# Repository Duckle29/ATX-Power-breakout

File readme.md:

# Pi ATX power breakout

This is just a simple board that breaks out the different rails of an ATX 24pin connector. It's mainly intented to be used for powering a Raspberry Pi and a 3D printer.

The board includes an EPS 4pin connector as well, allowing for up to 32A on the 12v rail. If you slightly overrun the rated 8A per cable, the 3 12v connectors will handle up to 36A (12A each). This is a 12.5% overload at 9A per cable. Most good cables/connectors should handle that.

The other rails can output 12A max, if the PSU can supply that on that rail.

The board also has a header for selecting how to control the PS_ON signal. It can either be controlled via a transistor controled by the RPi. Aditionally, the "Power Good" signal is also connected to the pi (through a voltage dividier).
Lastly, the I2C interface of the Pi is exposed on a 5 pin header, along with 5V 3V3 and Ground.

The 5V supply for the I2C connector and the Pi is selected through the the jumper JP1, while the 5V supply for the USB connector is selected via JP2. You can select between the 5V rail, or the 5V standby rail.

| Pin   | Function   |
|-------|------------|
| BCM17 | Power Good |
| BCM9  | Power On   |
| BCM26 | BTN to GND |

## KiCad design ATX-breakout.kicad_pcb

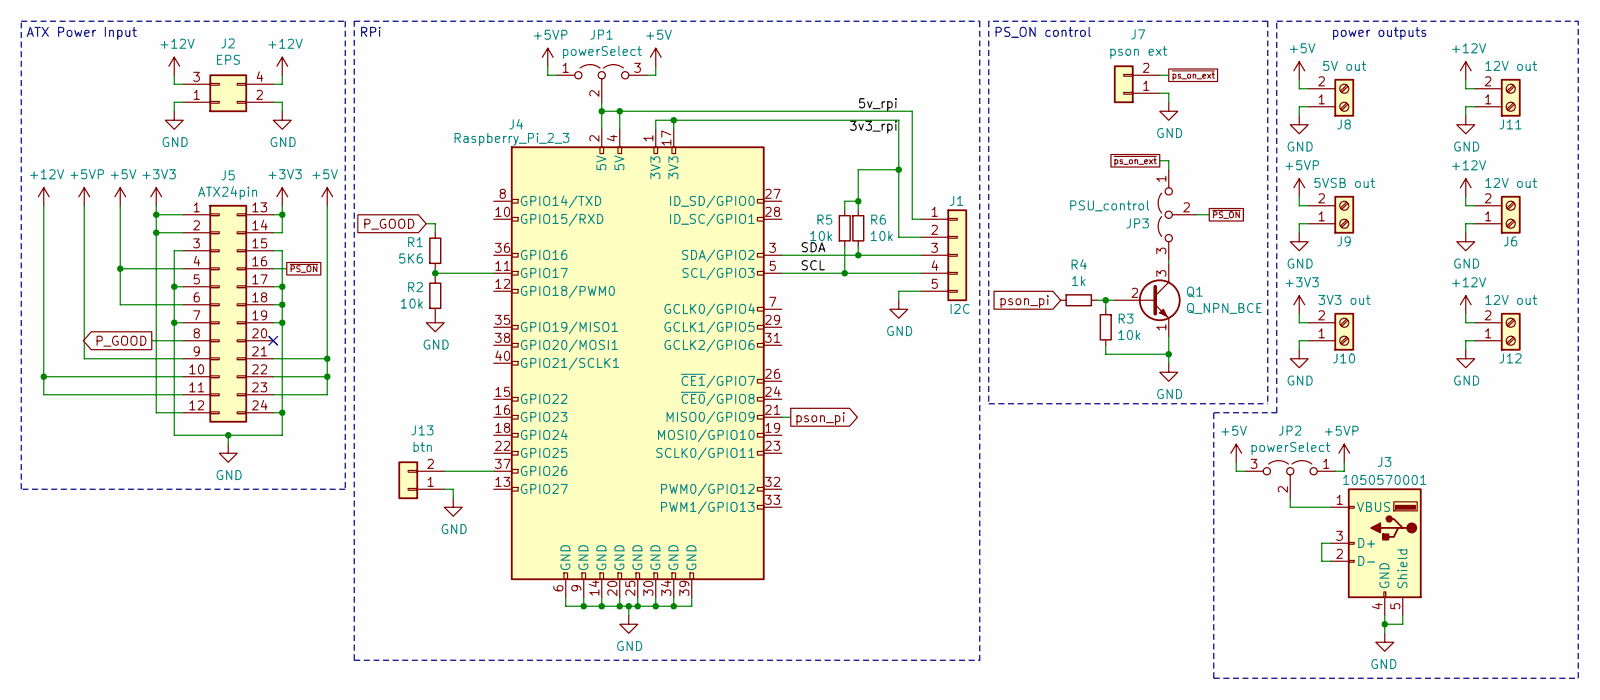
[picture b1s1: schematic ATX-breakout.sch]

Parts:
J1: I2C; PinHeader_1x05_P2.54mm_Vertical
J2: EPS; Molex_Mini-Fit_Jr_5566-04A_2x02_P4.20mm_Vertical
J3: 1050570001; USB_A_Molex_105057_Vertical
J4: Raspberry_Pi_2_3; PinSocket_2x20_P2.54mm_Vertical
J5: ATX24pin; Molex_Mini-Fit_Jr_5566-24A_2x12_P4.20mm_Vertical
J6, J11, J12: 12V out; PhoenixContact_MSTBA_2,5_2-G_1x02_P5.00mm_Horizontal
J7: pson ext; PinHeader_1x02_P2.54mm_Vertical
J8: 5V out; PhoenixContact_MSTBA_2,5_2-G_1x02_P5.00mm_Horizontal
J9: 5VSB out; PhoenixContact_MSTBA_2,5_2-G_1x02_P5.00mm_Horizontal
J10: 3V3 out; PhoenixContact_MSTBA_2,5_2-G_1x02_P5.00mm_Horizontal
J13: btn; PinHeader_1x02_P2.54mm_Vertical
JP1, JP2: powerSelect; PinHeader_1x03_P2.54mm_Vertical
JP3: PSU_control; PinHeader_1x03_P2.54mm_Vertical
Q1: Q_NPN_BCE; TO-92
R1: 5K6; R_Axial_DIN0207_L6.3mm_D2.5mm_P7.62mm_Horizontal
R2, R3, R5, R6: 10k; R_Axial_DIN0207_L6.3mm_D2.5mm_P7.62mm_Horizontal
R4: 1k; R_Axial_DIN0207_L6.3mm_D2.5mm_P7.62mm_Horizontal

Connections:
+3V3: J5.1, J5.2, J5.12, J5.13, J5.14, J10.2
+5V: J5.4, J5.6, J5.21, J5.22, J5.23, J8.2, JP1.3 (B), JP2.3 (B)
+5VP: J5.9, J9.2, JP1.1 (A), JP2.1 (A)
+12V: J2.3, J2.4, J5.10, J5.11, J6.2, J11.2, J12.2
/3v3_rpi: J1.2, J4.1 (3V3), J4.17 (3V3), R5.2, R6.1
/5v_rpi: J1.1, J4.2 (5V), J4.4 (5V), JP1.2 (C)
/SCL: J1.4, J4.5 (SCL/GPIO3), R5.1
/SDA: J1.3, J4.3 (SDA/GPIO2), R6.2
GND: J1.5, J2.1, J2.2, J3.4 (GND), J3.5 (Shield), J4.6 (GND), J4.9 (GND), J4.14 (GND), J4.20 (GND), J4.25 (GND), J4.30 (GND), J4.34 (GND), J4.39 (GND), J5.3, J5.5, J5.7, J5.15, J5.17, J5.18, J5.19, J5.24, J6.1, J7.1, J8.1, J9.1, J10.1, J11.1, J12.1, J13.1, Q1.1 (E), R2.1, R3.2
unnamed: J3.1 (VBUS), JP2.2 (C)
unnamed: J3.2 (D-), J3.3 (D+)
unnamed: J4.11 (GPIO17), R1.1, R2.2
unnamed: J4.37 (GPIO26), J13.2
unnamed: JP3.3 (B), Q1.3 (C)
unnamed: Q1.2 (B), R3.1, R4.2
P_GOOD: J5.8, R1.2
pson_pi: J4.21 (MISO0/GPIO9), R4.1
~PS_ON: J5.16, JP3.2 (C)
~ps_on_ext: J7.2, JP3.1 (A)

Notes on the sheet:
power outputs
PS_ON control
ATX Power Input
RPi

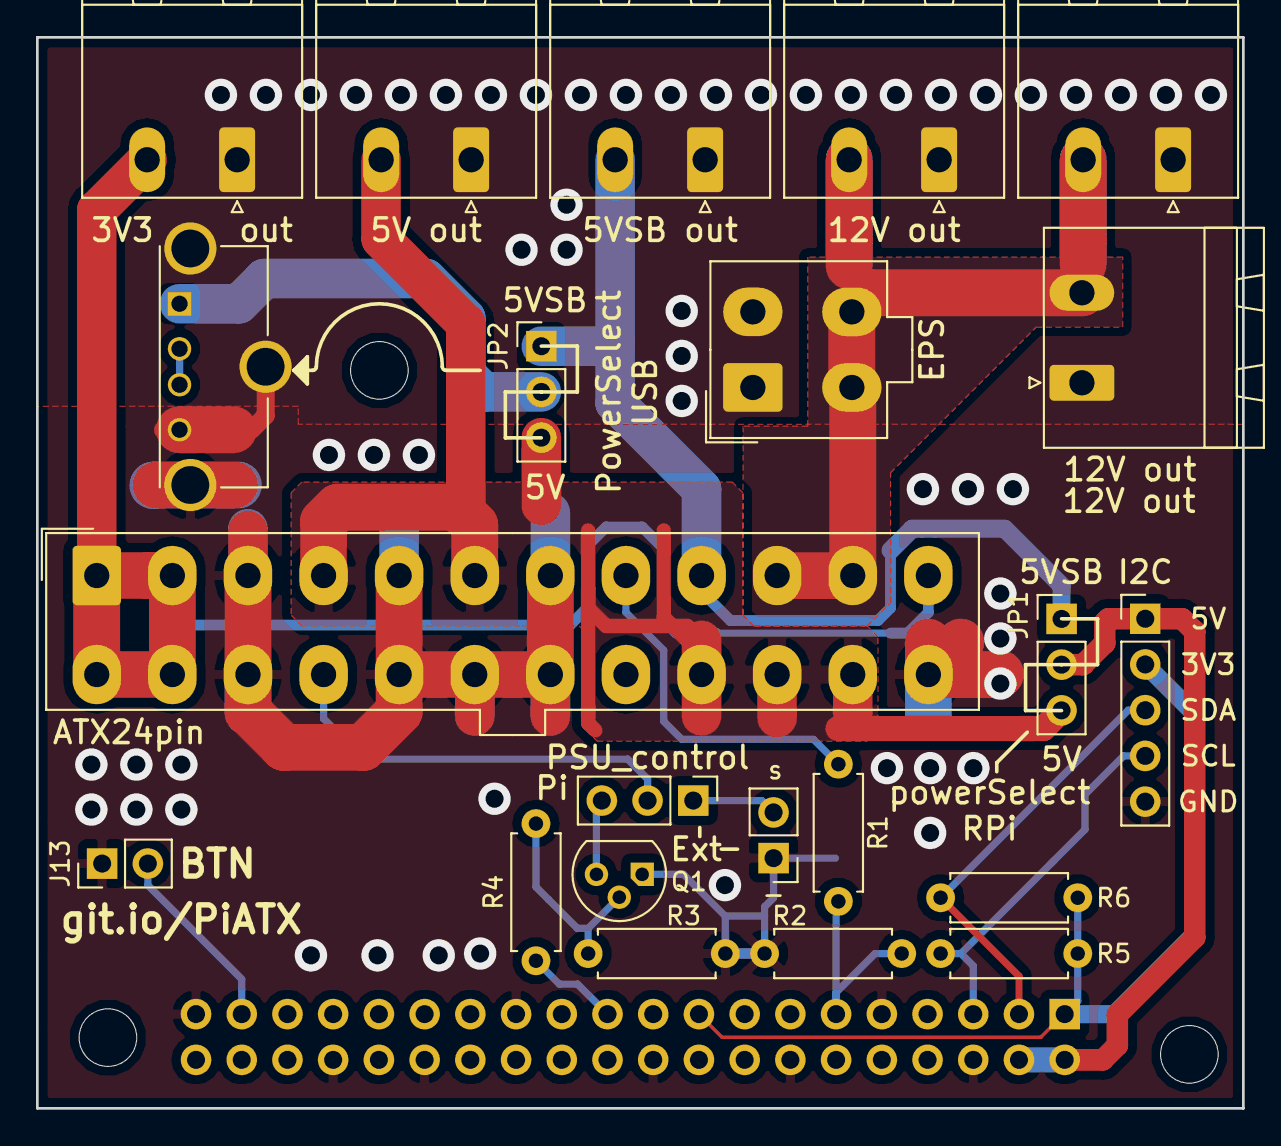
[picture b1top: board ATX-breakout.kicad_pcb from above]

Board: 2 copper layers, 67.0 x 59.5 mm, 23 parts (1 on the bottom side), 19 nets.

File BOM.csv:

"Id";"Designator";"Package";"Quantity";"Designation";"Supplier and ref";
1;"REF**,REF**,REF**";"MountingHole_3.2mm_M3_DIN965";3;"MountingHole_3.2mm_M3_DIN965";;;
2;"R4";"R_Axial_DIN0207_L6.3mm_D2.5mm_P7.62mm_Horizontal";1;"1k";;;
3;"J3";"USB_A_Stewart_SS-52100-001_Horizontal";1;"USB_A";;;
4;"G***,G***";"kiwi";2;"LOGO";;;
5;"J5";"Molex_Mini-Fit_Jr_5566-24A_2x12_P4.20mm_Vertical";1;"ATX24pin";;;
6;"J1";"PinHeader_1x05_P2.54mm_Vertical";1;"I2C";;;
7;"J2";"Molex_Mini-Fit_Jr_5566-04A_2x02_P4.20mm_Vertical";1;"EPS";;;
8;"J4";"PinSocket_2x20_P2.54mm_Vertical";1;"Raspberry_Pi_2_3";;;
9;"J7";"PinHeader_1x02_P2.54mm_Vertical";1;"pson ext";;;
10;"JP1,JP2";"PinHeader_1x03_P2.54mm_Vertical";2;"powerSelect";;;
11;"JP3";"PinHeader_1x03_P2.54mm_Vertical";1;"PSU_control";;;
12;"Q1";"TO-92";1;"Q_NPN_BCE";;;
13;"J6,J11,J12";"PhoenixContact_MSTBA_2,5_2-G_1x02_P5.00mm_Horizontal";3;"12V out";;;
14;"J8";"PhoenixContact_MSTBA_2,5_2-G_1x02_P5.00mm_Horizontal";1;"5V out";;;
15;"J9";"PhoenixContact_MSTBA_2,5_2-G_1x02_P5.00mm_Horizontal";1;"5VSB out";;;
16;"J10";"PhoenixContact_MSTBA_2,5_2-G_1x02_P5.00mm_Horizontal";1;"3V3 out";;;
17;"R1";"R_Axial_DIN0207_L6.3mm_D2.5mm_P7.62mm_Horizontal";1;"5K6";;;
18;"R2,R3,R5,R6";"R_Axial_DIN0207_L6.3mm_D2.5mm_P7.62mm_Horizontal";4;"10k";;;

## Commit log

2019-03-06 Added ignore
2019-03-06 removed bak files
2019-03-06 Finished up silkscreen
2019-03-06 added gerbers and BOM
2019-03-06 Added readme
2019-03-06 Made 12v pour solid, and increased 5v trace thicknesses
2019-03-06 updated top render
2019-03-06 Fixed 3.3v shorted across lots of pins
2019-03-06 fixed ground-pour weirdness
2019-03-15 Switched to a more common transistor pinout
2019-03-15 Create LICENSE
2019-03-18 Added third 12v connector, fixed 12v-5v short
2019-04-03 Added mounting holes
2019-04-04 added schematic PDF and updated BOM
2019-04-09 Updated silkscreen
2019-04-09 Testing out gpg signing
2019-04-09 rotated EPS and improved ground routing
2019-04-09 Updated silk screen and gerbers
2019-04-09 updated gerbers, silkscreen and renders
2019-04-09 Updated pdf and readme
2019-04-12 Switched to vertical USB to clear pi ethernet jack
2019-04-12 Fixed some accidentally large traces
